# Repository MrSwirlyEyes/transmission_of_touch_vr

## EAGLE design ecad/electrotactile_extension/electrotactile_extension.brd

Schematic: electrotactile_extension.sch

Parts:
C37, C49, C63, C64, C66, C68, C69, C70, C76, C78, C80: 0.1uF/50V; CAPC1005X55_SMD-0402
C61: 0.1uF/50V; CAPC1608X95
C62: 0.1uF/250V/0805; CAPC2012X95_SMD-0805
C65: 100uF/10V; CAPCP3216X160
C71, C72, C73, C75, C77, C79: 10uF/6.3V; CAPC1005X55_SMD-0402
C74: 4.7uF/10V/0402; CAPC1005X55_SMD-0402
ET_INDEX_PIXEL1-1, ET_INDEX_PIXEL1-2, ET_INDEX_PIXEL1-3, ET_INDEX_PIXEL1-4, ET_INDEX_PIXEL2-1, ET_INDEX_PIXEL2-2, ET_INDEX_PIXEL2-3, ET_INDEX_PIXEL2-4, ET_INDEX_PIXEL3-1, ET_INDEX_PIXEL3-2, ET_INDEX_PIXEL3-3, ET_INDEX_PIXEL3-4, ET_INDEX_PIXEL4-1, ET_INDEX_PIXEL4-2, ET_INDEX_PIXEL4-3, ET_INDEX_PIXEL4-4: SPST-NO 170mA 250V; SOP254P609X203-4
ET_MIDDLE_PIXEL1-1, ET_MIDDLE_PIXEL1-2, ET_MIDDLE_PIXEL1-3, ET_MIDDLE_PIXEL1-4, ET_MIDDLE_PIXEL2-1, ET_MIDDLE_PIXEL2-2, ET_MIDDLE_PIXEL2-3, ET_MIDDLE_PIXEL2-4, ET_MIDDLE_PIXEL3-1, ET_MIDDLE_PIXEL3-2, ET_MIDDLE_PIXEL3-3, ET_MIDDLE_PIXEL3-4, ET_MIDDLE_PIXEL4-1, ET_MIDDLE_PIXEL4-2, ET_MIDDLE_PIXEL4-3, ET_MIDDLE_PIXEL4-4: SPST-NO 170mA 250V; SOP254P609X203-4
ET_PINKY_PIXEL1-1, ET_PINKY_PIXEL1-2, ET_PINKY_PIXEL1-3, ET_PINKY_PIXEL1-4, ET_PINKY_PIXEL2-1, ET_PINKY_PIXEL2-2, ET_PINKY_PIXEL2-3, ET_PINKY_PIXEL2-4, ET_PINKY_PIXEL3-1, ET_PINKY_PIXEL3-2, ET_PINKY_PIXEL3-3, ET_PINKY_PIXEL3-4, ET_PINKY_PIXEL4-1, ET_PINKY_PIXEL4-2, ET_PINKY_PIXEL4-3, ET_PINKY_PIXEL4-4: SPST-NO 170mA 250V; SOP254P609X203-4
ET_RING_PIXEL1-1, ET_RING_PIXEL1-2, ET_RING_PIXEL1-3, ET_RING_PIXEL1-4, ET_RING_PIXEL2-1, ET_RING_PIXEL2-2, ET_RING_PIXEL2-3, ET_RING_PIXEL2-4, ET_RING_PIXEL3-1, ET_RING_PIXEL3-2, ET_RING_PIXEL3-3, ET_RING_PIXEL3-4, ET_RING_PIXEL4-1, ET_RING_PIXEL4-2, ET_RING_PIXEL4-3, ET_RING_PIXEL4-4: SPST-NO 170mA 250V; SOP254P609X203-4
IC1: DRV8662; QFN50P400X400X100-21T270
INDEX_CONNECTOR: 1x17 MOLEX SMD RA; 1X17_MOLEX_0532611771_RA_SMD
J6, J7, J8, J9: 1x02 PTH VERT FEMALE; HDRVR2W64P254_1X2_558X254X850B
L3: 4.7uH/2A/1008; INDC2520X100
L4: 10uH/380mA; INDC1608X60-0603
MIDDLE_CONNECTOR: 1x17 MOLEX SMD RA; 1X17_MOLEX_0532611771_RA_SMD
MUX_INDEX: PCA9685; SOP65P650X110-28
MUX_MIDDLE: PCA9685; SOP65P650X110-28
MUX_PINKY: PCA9685; SOP65P650X110-28
MUX_RING: PCA9685; SOP65P650X110-28
NFET1: 2N7002DW; SOT65P230X110-6
OPAMP4: TLV2361_GP_20MA_7MHZ; SOT95P280X145-5
PINKY_CONNECTOR: 1x17 MOLEX SMD RA; 1X17_MOLEX_0532611771_RA_SMD
POT1: 100K; POTENTIOMETER_SQ-L5-W4.5-H2.3
R1: 768K; RESC1005X35_SMD-0402
R2: 115K; RESC1005X35_SMD-0402
R4: 220K; RESC1005X35_SMD-0402
R5: 100K; RESC1005X35_SMD-0402
R49, R57, R58, R59, R60, R61, R62, R63, R64, R65, R66, R67, R68, R69, R70, R71, R88, R89, R90, R91, R92, R93, R94, R95, R96, R97, R98, R99, R100, R101, R102, R103, R104, R105, R106, R107, R108, R109, R110, R111, R112, R113, R114, R115, R116, R117, R118, R119, R120, R121, R122, R123, R124, R125, R126, R127, R128, R129, R130, R131, R132, R133, R134, R135: 1K; RESC1005X35_SMD-0402
R54, R55, R56, R136, R137: 10K; RESC1005X35_SMD-0402
REXT: 7.5K; RESC1005X35_SMD-0402
RING_CONNECTOR: 1x17 MOLEX SMD RA; 1X17_MOLEX_0532611771_RA_SMD
SW1, SW3, SW4: 300mA/4V; SW_SLIDE_SPDT_RA_SMD_4V_300MA_6.7L-2.6W
VREG2: NCP1729 50mA; SOT95P275X100-6
VREG3: TPS62202 300mA 1.8V; SOT95P280X145-5
VREG-MCU1: TPS76833QDR 1A/3.3V; SOIC127P600X265-8

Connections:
1.8V: C73.1, C75.1, L4.2, OPAMP4.5 (V+), VREG2.2 (VIN), VREG2.5 (!SHDN), VREG3.4 (NC/FB)
3.3V: C37.1, C61.1, C65.A, C66.1, C68.1, C69.1, C70.1, C74.1, C77.1, C78.1, IC1.2 (VDD), L3.2, MUX_INDEX.2 (A1), MUX_INDEX.28 (VCC), MUX_MIDDLE.1 (A0), MUX_MIDDLE.2 (A1), MUX_MIDDLE.28 (VCC), MUX_PINKY.1 (A0), MUX_PINKY.3 (A2), MUX_PINKY.28 (VCC), MUX_RING.3 (A2), MUX_RING.28 (VCC), SW1.2, SW3.2, SW4.2, VREG3.1 (VIN), VREG3.3 (EN), VREG-MCU1.5 (VOUT), VREG-MCU1.6 (VOUT)
-1.8V: C72.1, OPAMP4.2 (V-), VREG2.1 (VOUT)
C+: C71.1, VREG2.6 (C+)
C-: C71.2, VREG2.3 (C-)
EN: IC1.20 (EN), R54.2, SW1.3 (S2)
FB: IC1.3 (FB), R1.1, R2.2, R4.2, R5.2
GAIN0: IC1.18 (GAIN0), NFET1.5 (G2), R55.2, SW3.3 (S2)
GAIN1: IC1.19 (GAIN1), NFET1.2 (G1), R56.2, SW4.3 (S2)
GND: C37.2, C49.2, C61.2, C62.2, C63.1, C65.K, C66.2, C68.2, C69.2, C70.2, C72.2, C73.2, C74.2, C75.2, C76.2, C77.2, C78.2, C79.2, C80.2, IC1.4 (GND), IC1.5 (GND), IC1.6 (GND), IC1.9 (GND), IC1.EP (GND), IC1.P$1 (GND), IC1.P$2 (GND), IC1.P$3 (GND), IC1.P$4 (GND), J6.2, MUX_INDEX.1 (A0), MUX_INDEX.3 (A2), MUX_INDEX.4 (A3), MUX_INDEX.5 (A4), MUX_INDEX.14 (GND), MUX_INDEX.23 (!OE), MUX_INDEX.24 (A5), MUX_INDEX.25 (EXTCLK), MUX_MIDDLE.3 (A2), MUX_MIDDLE.4 (A3), MUX_MIDDLE.5 (A4), MUX_MIDDLE.14 (GND), MUX_MIDDLE.23 (!OE), MUX_MIDDLE.24 (A5), MUX_MIDDLE.25 (EXTCLK), MUX_PINKY.2 (A1), MUX_PINKY.4 (A3), MUX_PINKY.5 (A4), MUX_PINKY.14 (GND), MUX_PINKY.23 (!OE), MUX_PINKY.24 (A5), MUX_PINKY.25 (EXTCLK), MUX_RING.1 (A0), MUX_RING.2 (A1), MUX_RING.4 (A3), MUX_RING.5 (A4), MUX_RING.14 (GND), MUX_RING.23 (!OE), MUX_RING.24 (A5), MUX_RING.25 (EXTCLK), NFET1.1 (S1), NFET1.4 (S2), R2.1, R49.1, R54.1, R55.1, R56.1, R57.1, R58.1, R59.1, R60.1, R61.1, R62.1, R63.1, R64.1, R65.1, R66.1, R67.1, R68.1, R69.1, R70.1, R71.1, R88.1, R89.1, R90.1, R91.1, R92.1, R93.1, R94.1, R95.1, R96.1, R97.1, R98.1, R99.1, R100.1, R101.1, R102.1, R103.1, R104.1, R105.1, R106.1, R107.1, R108.1, R109.1, R110.1, R111.1, R112.1, R113.1, R114.1, R115.1, R116.1, R117.1, R118.1, R119.1, R120.1, R121.1, R122.1, R123.1, R124.1, R125.1, R126.1, R127.1, R128.1, R129.1, R130.1, R131.1, R132.1, R133.1, R134.1, R135.1, R137.1, REXT.1, VREG2.4 (GND), VREG3.2 (GND), VREG-MCU1.1 (GND), VREG-MCU1.2 (!EN)
IN+: C64.1, OPAMP4.4 (OUT), POT1.1 (CCW), POT1.2 (S), R136.2
INDEX_IN1-1: ET_INDEX_PIXEL1-1.1, MUX_INDEX.6 (PWM0)
INDEX_IN1-2: ET_INDEX_PIXEL1-2.1, MUX_INDEX.8 (PWM2)
INDEX_IN1-3: ET_INDEX_PIXEL1-3.1, MUX_INDEX.10 (PWM4)
INDEX_IN1-4: ET_INDEX_PIXEL1-4.1, MUX_INDEX.12 (PWM6)
INDEX_IN2-1: ET_INDEX_PIXEL2-1.1, MUX_INDEX.7 (PWM1)
INDEX_IN2-2: ET_INDEX_PIXEL2-2.1, MUX_INDEX.9 (PWM3)
INDEX_IN2-3: ET_INDEX_PIXEL2-3.1, MUX_INDEX.11 (PWM5)
INDEX_IN2-4: ET_INDEX_PIXEL2-4.1, MUX_INDEX.13 (PWM7)
INDEX_IN3-1: ET_INDEX_PIXEL3-1.1, MUX_INDEX.15 (PWM8)
INDEX_IN3-2: ET_INDEX_PIXEL3-2.1, MUX_INDEX.17 (PWM10)
INDEX_IN3-3: ET_INDEX_PIXEL3-3.1, MUX_INDEX.19 (PWM12)
INDEX_IN3-4: ET_INDEX_PIXEL3-4.1, MUX_INDEX.21 (PWM14)
INDEX_IN4-1: ET_INDEX_PIXEL4-1.1, MUX_INDEX.16 (PWM9)
INDEX_IN4-2: ET_INDEX_PIXEL4-2.1, MUX_INDEX.18 (PWM11)
INDEX_IN4-3: ET_INDEX_PIXEL4-3.1, MUX_INDEX.20 (PWM13)
INDEX_IN4-4: ET_INDEX_PIXEL4-4.1, MUX_INDEX.22 (PWM15)
INDEX_OUT1-1: ET_INDEX_PIXEL1-1.3, INDEX_CONNECTOR.1
INDEX_OUT1-2: ET_INDEX_PIXEL1-2.3, INDEX_CONNECTOR.3
INDEX_OUT1-3: ET_INDEX_PIXEL1-3.3, INDEX_CONNECTOR.5
INDEX_OUT1-4: ET_INDEX_PIXEL1-4.3, INDEX_CONNECTOR.7
INDEX_OUT2-1: ET_INDEX_PIXEL2-1.3, INDEX_CONNECTOR.2
INDEX_OUT2-2: ET_INDEX_PIXEL2-2.3, INDEX_CONNECTOR.4
INDEX_OUT2-3: ET_INDEX_PIXEL2-3.3, INDEX_CONNECTOR.6
INDEX_OUT2-4: ET_INDEX_PIXEL2-4.3, INDEX_CONNECTOR.8
INDEX_OUT3-1: ET_INDEX_PIXEL3-1.3, INDEX_CONNECTOR.9
INDEX_OUT3-2: ET_INDEX_PIXEL3-2.3, INDEX_CONNECTOR.11
INDEX_OUT3-3: ET_INDEX_PIXEL3-3.3, INDEX_CONNECTOR.13
INDEX_OUT3-4: ET_INDEX_PIXEL3-4.3, INDEX_CONNECTOR.15
INDEX_OUT4-1: ET_INDEX_PIXEL4-1.3, INDEX_CONNECTOR.10
INDEX_OUT4-2: ET_INDEX_PIXEL4-2.3, INDEX_CONNECTOR.12
INDEX_OUT4-3: ET_INDEX_PIXEL4-3.3, INDEX_CONNECTOR.14
INDEX_OUT4-4: ET_INDEX_PIXEL4-4.3, INDEX_CONNECTOR.16
MIDDLE_IN1-1: ET_MIDDLE_PIXEL1-1.1, MUX_MIDDLE.21 (PWM14)
MIDDLE_IN1-2: ET_MIDDLE_PIXEL1-2.1, MUX_MIDDLE.19 (PWM12)
MIDDLE_IN1-3: ET_MIDDLE_PIXEL1-3.1, MUX_MIDDLE.17 (PWM10)
MIDDLE_IN1-4: ET_MIDDLE_PIXEL1-4.1, MUX_MIDDLE.15 (PWM8)
MIDDLE_IN2-1: ET_MIDDLE_PIXEL2-1.1, MUX_MIDDLE.22 (PWM15)
MIDDLE_IN2-2: ET_MIDDLE_PIXEL2-2.1, MUX_MIDDLE.20 (PWM13)
MIDDLE_IN2-3: ET_MIDDLE_PIXEL2-3.1, MUX_MIDDLE.18 (PWM11)
MIDDLE_IN2-4: ET_MIDDLE_PIXEL2-4.1, MUX_MIDDLE.16 (PWM9)
MIDDLE_IN3-1: ET_MIDDLE_PIXEL3-1.1, MUX_MIDDLE.12 (PWM6)
MIDDLE_IN3-2: ET_MIDDLE_PIXEL3-2.1, MUX_MIDDLE.10 (PWM4)
MIDDLE_IN3-3: ET_MIDDLE_PIXEL3-3.1, MUX_MIDDLE.8 (PWM2)
MIDDLE_IN3-4: ET_MIDDLE_PIXEL3-4.1, MUX_MIDDLE.6 (PWM0)
MIDDLE_IN4-1: ET_MIDDLE_PIXEL4-1.1, MUX_MIDDLE.13 (PWM7)
MIDDLE_IN4-2: ET_MIDDLE_PIXEL4-2.1, MUX_MIDDLE.11 (PWM5)
MIDDLE_IN4-3: ET_MIDDLE_PIXEL4-3.1, MUX_MIDDLE.9 (PWM3)
MIDDLE_IN4-4: ET_MIDDLE_PIXEL4-4.1, MUX_MIDDLE.7 (PWM1)
MIDDLE_OUT1-1: ET_MIDDLE_PIXEL1-1.3, MIDDLE_CONNECTOR.16
MIDDLE_OUT1-2: ET_MIDDLE_PIXEL1-2.3, MIDDLE_CONNECTOR.14
MIDDLE_OUT1-3: ET_MIDDLE_PIXEL1-3.3, MIDDLE_CONNECTOR.12
MIDDLE_OUT1-4: ET_MIDDLE_PIXEL1-4.3, MIDDLE_CONNECTOR.10
MIDDLE_OUT2-1: ET_MIDDLE_PIXEL2-1.3, MIDDLE_CONNECTOR.17
MIDDLE_OUT2-2: ET_MIDDLE_PIXEL2-2.3, MIDDLE_CONNECTOR.15
MIDDLE_OUT2-3: ET_MIDDLE_PIXEL2-3.3, MIDDLE_CONNECTOR.13
MIDDLE_OUT2-4: ET_MIDDLE_PIXEL2-4.3, MIDDLE_CONNECTOR.11
MIDDLE_OUT3-1: ET_MIDDLE_PIXEL3-1.3, MIDDLE_CONNECTOR.8
MIDDLE_OUT3-2: ET_MIDDLE_PIXEL3-2.3, MIDDLE_CONNECTOR.6
MIDDLE_OUT3-3: ET_MIDDLE_PIXEL3-3.3, MIDDLE_CONNECTOR.4
MIDDLE_OUT3-4: ET_MIDDLE_PIXEL3-4.3, MIDDLE_CONNECTOR.2
MIDDLE_OUT4-1: ET_MIDDLE_PIXEL4-1.3, MIDDLE_CONNECTOR.9
MIDDLE_OUT4-2: ET_MIDDLE_PIXEL4-2.3, MIDDLE_CONNECTOR.7
MIDDLE_OUT4-3: ET_MIDDLE_PIXEL4-3.3, MIDDLE_CONNECTOR.5
MIDDLE_OUT4-4: ET_MIDDLE_PIXEL4-4.3, MIDDLE_CONNECTOR.3
unnamed: ET_INDEX_PIXEL1-3.2, R58.2
unnamed: ET_INDEX_PIXEL1-1.2, R49.2
unnamed: IC1.7 (SW), IC1.8 (SW), L3.1
unnamed: C49.1, IC1.1 (VPUMP)
unnamed: C62.1, IC1.10 (VBST), IC1.11 (VBST), IC1.12 (PVDD), R1.2
unnamed: IC1.15 (REXT), REXT.2
unnamed: NFET1.6 (D1), R4.1
unnamed: NFET1.3 (D2), R5.1
unnamed: C64.2, IC1.17 (IN+)
unnamed: C63.2, IC1.16 (IN-)
unnamed: ET_INDEX_PIXEL1-2.2, R57.2
unnamed: ET_INDEX_PIXEL1-4.2, R59.2
unnamed: ET_INDEX_PIXEL2-1.2, R60.2
unnamed: ET_INDEX_PIXEL2-2.2, R61.2
unnamed: ET_INDEX_PIXEL2-3.2, R62.2
unnamed: ET_INDEX_PIXEL2-4.2, R63.2
unnamed: ET_INDEX_PIXEL3-1.2, R64.2
unnamed: ET_INDEX_PIXEL3-2.2, R65.2
unnamed: ET_INDEX_PIXEL3-3.2, R66.2
unnamed: ET_INDEX_PIXEL3-4.2, R67.2
unnamed: ET_INDEX_PIXEL4-1.2, R68.2
unnamed: ET_INDEX_PIXEL4-2.2, R69.2
unnamed: ET_INDEX_PIXEL4-3.2, R70.2
unnamed: ET_INDEX_PIXEL4-4.2, R71.2
unnamed: ET_MIDDLE_PIXEL1-1.2, R88.2
unnamed: ET_MIDDLE_PIXEL1-2.2, R89.2
unnamed: ET_MIDDLE_PIXEL1-3.2, R90.2
unnamed: ET_MIDDLE_PIXEL1-4.2, R91.2
unnamed: ET_MIDDLE_PIXEL2-1.2, R92.2
unnamed: ET_MIDDLE_PIXEL2-2.2, R93.2
unnamed: ET_MIDDLE_PIXEL2-3.2, R94.2
unnamed: ET_MIDDLE_PIXEL2-4.2, R95.2
unnamed: ET_MIDDLE_PIXEL3-1.2, R96.2
unnamed: ET_MIDDLE_PIXEL3-2.2, R97.2
unnamed: ET_MIDDLE_PIXEL3-3.2, R98.2
unnamed: ET_MIDDLE_PIXEL3-4.2, R99.2
unnamed: ET_MIDDLE_PIXEL4-1.2, R100.2
unnamed: ET_MIDDLE_PIXEL4-2.2, R101.2
unnamed: ET_MIDDLE_PIXEL4-3.2, R102.2
unnamed: ET_MIDDLE_PIXEL4-4.2, R103.2
unnamed: ET_RING_PIXEL1-1.2, R104.2
unnamed: ET_RING_PIXEL1-2.2, R105.2
unnamed: ET_RING_PIXEL1-3.2, R106.2
unnamed: ET_RING_PIXEL1-4.2, R107.2
unnamed: ET_RING_PIXEL2-1.2, R108.2
unnamed: ET_RING_PIXEL2-2.2, R109.2
unnamed: ET_RING_PIXEL2-3.2, R110.2
unnamed: ET_RING_PIXEL2-4.2, R111.2
unnamed: ET_RING_PIXEL3-1.2, R112.2
unnamed: ET_RING_PIXEL3-2.2, R113.2
unnamed: ET_RING_PIXEL3-3.2, R114.2
unnamed: ET_RING_PIXEL3-4.2, R115.2
unnamed: ET_RING_PIXEL4-1.2, R116.2
unnamed: ET_RING_PIXEL4-2.2, R117.2
unnamed: ET_RING_PIXEL4-3.2, R118.2
unnamed: ET_RING_PIXEL4-4.2, R119.2
unnamed: ET_PINKY_PIXEL1-1.2, R120.2
unnamed: ET_PINKY_PIXEL1-2.2, R121.2
unnamed: ET_PINKY_PIXEL1-3.2, R122.2
unnamed: ET_PINKY_PIXEL1-4.2, R123.2
unnamed: ET_PINKY_PIXEL2-1.2, R124.2
unnamed: ET_PINKY_PIXEL2-2.2, R125.2
unnamed: ET_PINKY_PIXEL2-3.2, R126.2
unnamed: ET_PINKY_PIXEL2-4.2, R127.2
unnamed: ET_PINKY_PIXEL3-1.2, R128.2
unnamed: ET_PINKY_PIXEL3-2.2, R129.2
unnamed: ET_PINKY_PIXEL3-3.2, R130.2
unnamed: ET_PINKY_PIXEL3-4.2, R131.2
unnamed: ET_PINKY_PIXEL4-1.2, R132.2
unnamed: ET_PINKY_PIXEL4-2.2, R133.2
unnamed: ET_PINKY_PIXEL4-3.2, R134.2
unnamed: ET_PINKY_PIXEL4-4.2, R135.2
unnamed: L4.1, VREG3.5 (VOUT)
unnamed: OPAMP4.1 (IN+), R136.1, R137.2
unnamed: C76.1, OPAMP4.3 (IN-), POT1.3 (CW)
PINKY_IN1-1: ET_PINKY_PIXEL1-1.1, MUX_PINKY.22 (PWM15)
PINKY_IN1-2: ET_PINKY_PIXEL1-2.1, MUX_PINKY.20 (PWM13)
PINKY_IN1-3: ET_PINKY_PIXEL1-3.1, MUX_PINKY.18 (PWM11)
PINKY_IN1-4: ET_PINKY_PIXEL1-4.1, MUX_PINKY.16 (PWM9)
PINKY_IN2-1: ET_PINKY_PIXEL2-1.1, MUX_PINKY.21 (PWM14)
PINKY_IN2-2: ET_PINKY_PIXEL2-2.1, MUX_PINKY.19 (PWM12)
PINKY_IN2-3: ET_PINKY_PIXEL2-3.1, MUX_PINKY.17 (PWM10)
PINKY_IN2-4: ET_PINKY_PIXEL2-4.1, MUX_PINKY.15 (PWM8)
PINKY_IN3-1: ET_PINKY_PIXEL3-1.1, MUX_PINKY.13 (PWM7)
PINKY_IN3-2: ET_PINKY_PIXEL3-2.1, MUX_PINKY.11 (PWM5)
PINKY_IN3-3: ET_PINKY_PIXEL3-3.1, MUX_PINKY.9 (PWM3)
PINKY_IN3-4: ET_PINKY_PIXEL3-4.1, MUX_PINKY.7 (PWM1)
PINKY_IN4-1: ET_PINKY_PIXEL4-1.1, MUX_PINKY.12 (PWM6)
PINKY_IN4-2: ET_PINKY_PIXEL4-2.1, MUX_PINKY.10 (PWM4)
PINKY_IN4-3: ET_PINKY_PIXEL4-3.1, MUX_PINKY.8 (PWM2)
PINKY_IN4-4: ET_PINKY_PIXEL4-4.1, MUX_PINKY.6 (PWM0)
PINKY_OUT1-1: ET_PINKY_PIXEL1-1.3, PINKY_CONNECTOR.16
PINKY_OUT1-2: ET_PINKY_PIXEL1-2.3, PINKY_CONNECTOR.14
PINKY_OUT1-3: ET_PINKY_PIXEL1-3.3, PINKY_CONNECTOR.12
PINKY_OUT1-4: ET_PINKY_PIXEL1-4.3, PINKY_CONNECTOR.10
PINKY_OUT2-1: ET_PINKY_PIXEL2-1.3, PINKY_CONNECTOR.17
PINKY_OUT2-2: ET_PINKY_PIXEL2-2.3, PINKY_CONNECTOR.15
PINKY_OUT2-3: ET_PINKY_PIXEL2-3.3, PINKY_CONNECTOR.13
PINKY_OUT2-4: ET_PINKY_PIXEL2-4.3, PINKY_CONNECTOR.11
PINKY_OUT3-1: ET_PINKY_PIXEL3-1.3, PINKY_CONNECTOR.8
PINKY_OUT3-2: ET_PINKY_PIXEL3-2.3, PINKY_CONNECTOR.6
PINKY_OUT3-3: ET_PINKY_PIXEL3-3.3, PINKY_CONNECTOR.4
PINKY_OUT3-4: ET_PINKY_PIXEL3-4.3, PINKY_CONNECTOR.2
PINKY_OUT4-1: ET_PINKY_PIXEL4-1.3, PINKY_CONNECTOR.9
PINKY_OUT4-2: ET_PINKY_PIXEL4-2.3, PINKY_CONNECTOR.7
PINKY_OUT4-3: ET_PINKY_PIXEL4-3.3, PINKY_CONNECTOR.5
PINKY_OUT4-4: ET_PINKY_PIXEL4-4.3, PINKY_CONNECTOR.3
RING_IN1-1: ET_RING_PIXEL1-1.1, MUX_RING.7 (PWM1)
RING_IN1-2: ET_RING_PIXEL1-2.1, MUX_RING.9 (PWM3)
RING_IN1-3: ET_RING_PIXEL1-3.1, MUX_RING.11 (PWM5)
RING_IN1-4: ET_RING_PIXEL1-4.1, MUX_RING.13 (PWM7)
RING_IN2-1: ET_RING_PIXEL2-1.1, MUX_RING.6 (PWM0)
RING_IN2-2: ET_RING_PIXEL2-2.1, MUX_RING.8 (PWM2)
RING_IN2-3: ET_RING_PIXEL2-3.1, MUX_RING.10 (PWM4)
RING_IN2-4: ET_RING_PIXEL2-4.1, MUX_RING.12 (PWM6)
RING_IN3-1: ET_RING_PIXEL3-1.1, MUX_RING.16 (PWM9)
RING_IN3-2: ET_RING_PIXEL3-2.1, MUX_RING.18 (PWM11)
RING_IN3-3: ET_RING_PIXEL3-3.1, MUX_RING.20 (PWM13)
RING_IN3-4: ET_RING_PIXEL3-4.1, MUX_RING.22 (PWM15)
RING_IN4-1: ET_RING_PIXEL4-1.1, MUX_RING.15 (PWM8)
RING_IN4-2: ET_RING_PIXEL4-2.1, MUX_RING.17 (PWM10)
RING_IN4-3: ET_RING_PIXEL4-3.1, MUX_RING.19 (PWM12)
RING_IN4-4: ET_RING_PIXEL4-4.1, MUX_RING.21 (PWM14)
RING_OUT1-1: ET_RING_PIXEL1-1.3, RING_CONNECTOR.1
RING_OUT1-2: ET_RING_PIXEL1-2.3, RING_CONNECTOR.3
RING_OUT1-3: ET_RING_PIXEL1-3.3, RING_CONNECTOR.5
RING_OUT1-4: ET_RING_PIXEL1-4.3, RING_CONNECTOR.7
RING_OUT2-1: ET_RING_PIXEL2-1.3, RING_CONNECTOR.2
RING_OUT2-2: ET_RING_PIXEL2-2.3, RING_CONNECTOR.4
RING_OUT2-3: ET_RING_PIXEL2-3.3, RING_CONNECTOR.6
RING_OUT2-4: ET_RING_PIXEL2-4.3, RING_CONNECTOR.8
RING_OUT3-1: ET_RING_PIXEL3-1.3, RING_CONNECTOR.9
RING_OUT3-2: ET_RING_PIXEL3-2.3, RING_CONNECTOR.11
RING_OUT3-3: ET_RING_PIXEL3-3.3, RING_CONNECTOR.13
RING_OUT3-4: ET_RING_PIXEL3-4.3, RING_CONNECTOR.15
RING_OUT4-1: ET_RING_PIXEL4-1.3, RING_CONNECTOR.10
RING_OUT4-2: ET_RING_PIXEL4-2.3, RING_CONNECTOR.12
RING_OUT4-3: ET_RING_PIXEL4-3.3, RING_CONNECTOR.14
RING_OUT4-4: ET_RING_PIXEL4-4.3, RING_CONNECTOR.16
SCL: J7.2, MUX_INDEX.26 (SCL), MUX_MIDDLE.26 (SCL), MUX_PINKY.26 (SCL), MUX_RING.26 (SCL)
SDA: J7.1, MUX_INDEX.27 (SDA), MUX_MIDDLE.27 (SDA), MUX_PINKY.27 (SDA), MUX_RING.27 (SDA)
V+: ET_INDEX_PIXEL1-1.4, ET_INDEX_PIXEL1-2.4, ET_INDEX_PIXEL1-3.4, ET_INDEX_PIXEL1-4.4, ET_INDEX_PIXEL2-1.4, ET_INDEX_PIXEL2-2.4, ET_INDEX_PIXEL2-3.4, ET_INDEX_PIXEL2-4.4, ET_INDEX_PIXEL3-1.4, ET_INDEX_PIXEL3-2.4, ET_INDEX_PIXEL3-3.4, ET_INDEX_PIXEL3-4.4, ET_INDEX_PIXEL4-1.4, ET_INDEX_PIXEL4-2.4, ET_INDEX_PIXEL4-3.4, ET_INDEX_PIXEL4-4.4, ET_MIDDLE_PIXEL1-1.4, ET_MIDDLE_PIXEL1-2.4, ET_MIDDLE_PIXEL1-3.4, ET_MIDDLE_PIXEL1-4.4, ET_MIDDLE_PIXEL2-1.4, ET_MIDDLE_PIXEL2-2.4, ET_MIDDLE_PIXEL2-3.4, ET_MIDDLE_PIXEL2-4.4, ET_MIDDLE_PIXEL3-1.4, ET_MIDDLE_PIXEL3-2.4, ET_MIDDLE_PIXEL3-3.4, ET_MIDDLE_PIXEL3-4.4, ET_MIDDLE_PIXEL4-1.4, ET_MIDDLE_PIXEL4-2.4, ET_MIDDLE_PIXEL4-3.4, ET_MIDDLE_PIXEL4-4.4, ET_PINKY_PIXEL1-1.4, ET_PINKY_PIXEL1-2.4, ET_PINKY_PIXEL1-3.4, ET_PINKY_PIXEL1-4.4, ET_PINKY_PIXEL2-1.4, ET_PINKY_PIXEL2-2.4, ET_PINKY_PIXEL2-3.4, ET_PINKY_PIXEL2-4.4, ET_PINKY_PIXEL3-1.4, ET_PINKY_PIXEL3-2.4, ET_PINKY_PIXEL3-3.4, ET_PINKY_PIXEL3-4.4, ET_PINKY_PIXEL4-1.4, ET_PINKY_PIXEL4-2.4, ET_PINKY_PIXEL4-3.4, ET_PINKY_PIXEL4-4.4, ET_RING_PIXEL1-1.4, ET_RING_PIXEL1-2.4, ET_RING_PIXEL1-3.4, ET_RING_PIXEL1-4.4, ET_RING_PIXEL2-1.4, ET_RING_PIXEL2-2.4, ET_RING_PIXEL2-3.4, ET_RING_PIXEL2-4.4, ET_RING_PIXEL3-1.4, ET_RING_PIXEL3-2.4, ET_RING_PIXEL3-3.4, ET_RING_PIXEL3-4.4, ET_RING_PIXEL4-1.4, ET_RING_PIXEL4-2.4, ET_RING_PIXEL4-3.4, ET_RING_PIXEL4-4.4, IC1.13 (OUT+)
V-: IC1.14 (OUT-), INDEX_CONNECTOR.17, MIDDLE_CONNECTOR.1, PINKY_CONNECTOR.1, RING_CONNECTOR.17
VBAT: C79.1, C80.1, J6.1, VREG-MCU1.3 (VIN), VREG-MCU1.4 (VIN)

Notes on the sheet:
TRANSMISSION OF TOUCH VR
TOUCH GLOVE
Rev 3
Designed by: MrSwirlyEyes
ANALOG VOLTAGE AMPLIFIER
ET ARRAY - INDEX
ET ARRAY - MIDDLE
0x44
ET ARRAY - RING
0x45
ET ARRAY - PINKY
SQW GENERATOR
ELECTROTACTILE ARRAYS
STAGE1
STAGE2
STAGE3
+3.3V VREG
+1.8V VREG
-1.8V VREG
0x42
0x43

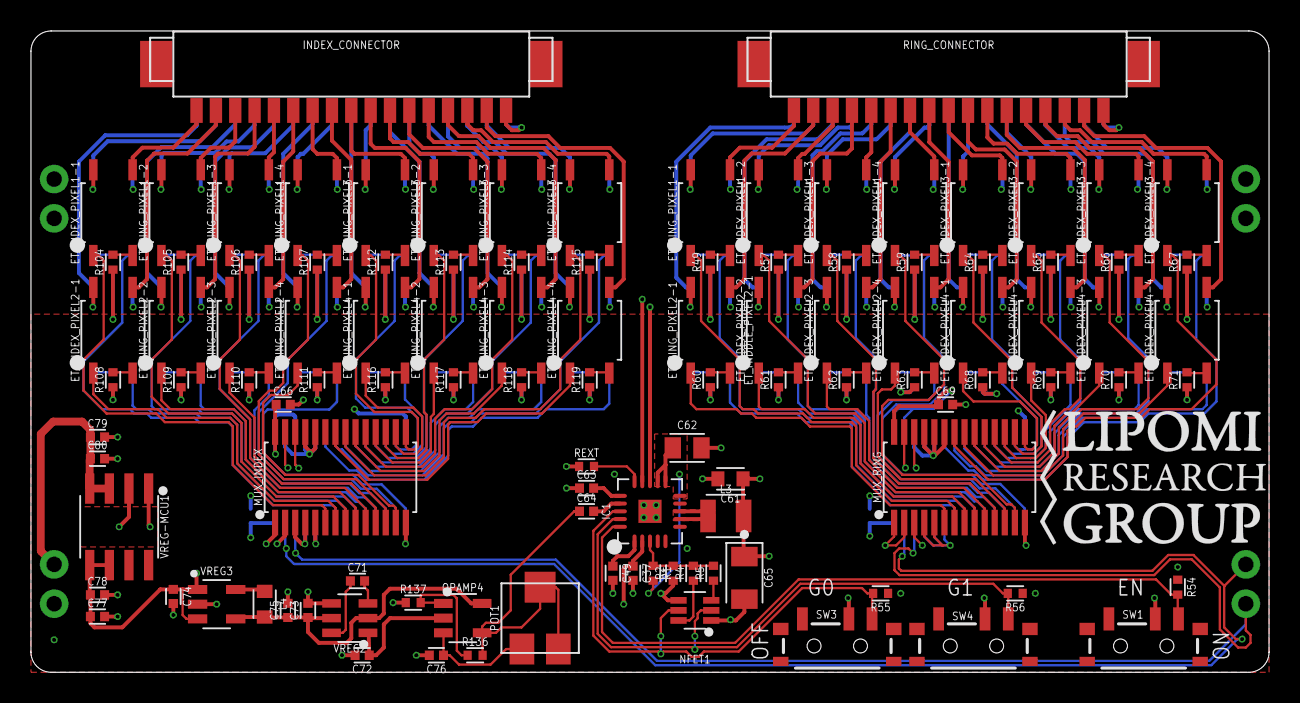
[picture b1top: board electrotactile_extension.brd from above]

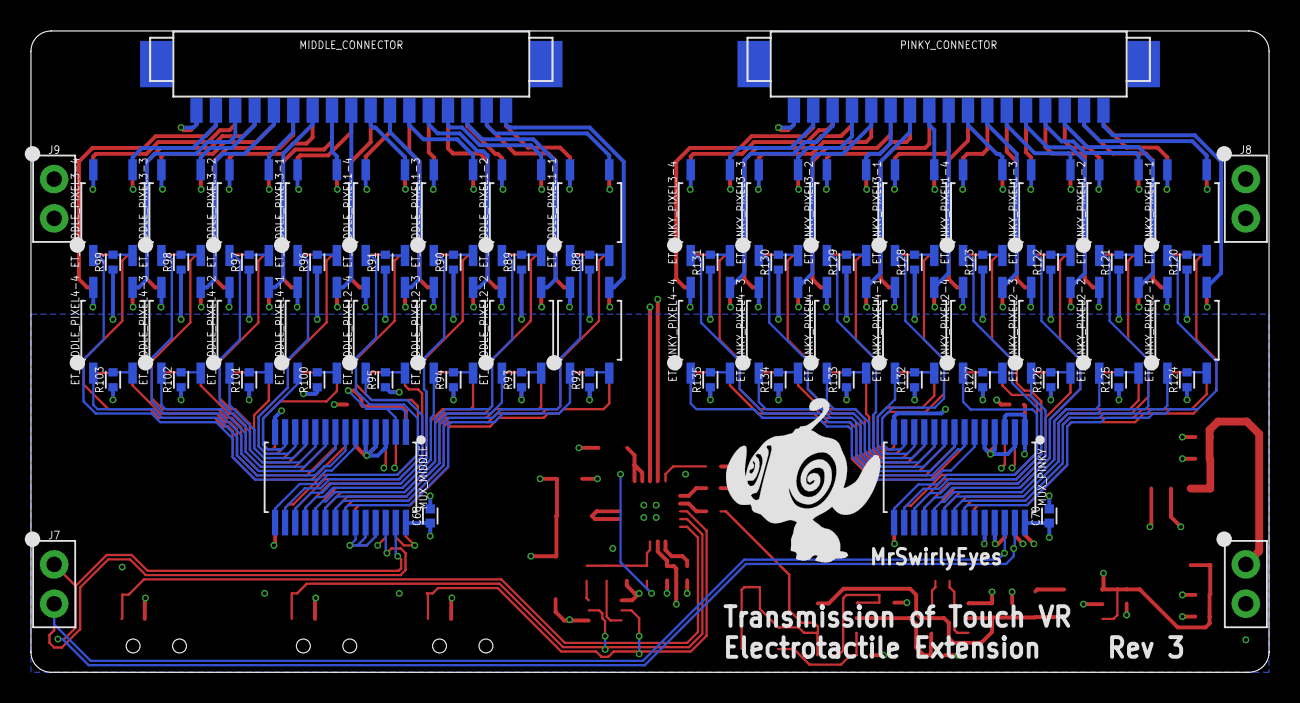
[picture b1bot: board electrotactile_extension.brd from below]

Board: 4 copper layers, 80.0 x 41.4 mm, 185 parts (75 on the bottom side), 219 nets.

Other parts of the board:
U$1: LRG-LOGO-2
U$2: MRSWIRLYEYES-LOGO

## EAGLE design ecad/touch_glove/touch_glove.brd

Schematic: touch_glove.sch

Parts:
ANT: 2.45GHz; ANTC6522X100
AVR_ISP: AVR ISP; HDRV6W64P254_2X3_762X508X838B
BALUN1: 50/100; RESCAXE65P200X125X95-6
BL_CONNECTOR: PTH VERT MALE; HDRV2W64P254_1X2_508X254X838B
BR_ANALOG: NET_BRIDGE
BR_CONNECTOR: PTH VERT MALE; HDRV2W64P254_1X2_508X254X838B
BR_NOISE: NET_BRIDGE
C1, C2, C3, C18, C21: 100uF/10V; CAPCP3216X160
C4, C6, C8, C11, C12, C15: 10uF/6.3V; CAPC1005X55_SMD-0402
C5, C7, C9, C10, C13, C14, C22, C23, C25, C27, C30, C38, C44, C45, C46, C47, C48, C50, C51, C52, C53, C54, C55, C56, C57, C58, C59, C60: 0.1uF/50V; CAPC1005X55_SMD-0402
C24, C26, C28, C29, C31, C32: 1uF/25V; CAPC1005X55_SMD-0402
C33, C34: 12pF/100V; CAPC1005X55_SMD-0402
C35: 0.75pF/50V; CAPC1005X55_SMD-0402
C36: 22pF/100V/0402; CAPC1005X55_SMD-0402
D2, D3: 1A/50V; SODFL3516X170
D4, D5, D6, D7, D8, D9, D10: 150mA/75V; DFN100X60X55-2
DEMUX1: CH16_MUX-DEMUX; SOP65P780X200-24
FLEX-INDEX: 10K; _MOLEX-0530470210_VERT_PITCH-1.25MM
FLEX-MIDDLE: 10K; _MOLEX-0530470210_VERT_PITCH-1.25MM
FLEX-PINKY: 10K; _MOLEX-0530470210_VERT_PITCH-1.25MM
FLEX-RING: 10K; _MOLEX-0530470210_VERT_PITCH-1.25MM
FLEX-THUMB: 10K; _MOLEX-0530470210_VERT_PITCH-1.25MM
FTDI: PTH RA VERT MALE; HDRRA6W64P254_1X6_1524X254X254B_FTDI
HBRIDGE-INDEX: DRV8837C 1A; WSON-8-PPAD
HBRIDGE-MIDDLE: DRV8837C 1A; WSON-8-PPAD
HBRIDGE-PINKY: DRV8837C 1A; WSON-8-PPAD
HBRIDGE-RING: DRV8837C 1A; WSON-8-PPAD
HBRIDGE-THUMB: DRV8837C 1A; WSON-8-PPAD
J9: PTH VERT MALE; HDRV2W64P254_1X2_508X254X838B
JP1: JUMPER_SMD_3-PAD_NO_SILK; SMT-JUMPER_3_NO_SILK
L1, L2: 10uH/380mA; INDC1608X60-0603
LED1: BLUE; LEDC1005X40_LED-0402
LED2: GREEN; LEDC1005X40_LED-0402
LED3: RED; LEDC1005X40_LED-0402
LIPO1: 7.4V; BATTERY_MOLEX-0530470210_VERT_PITCH-1.25MM
MCU: ATMEGA128RFA1; QFN50P900X900X90-64
OPAMP1, OPAMP2, OPAMP3: LM358; WSON-8-PPAD
PWM_DRIVER1: PCA9685; SOP65P650X110-28
Q1, Q2, Q3, Q4, Q5, Q6: MCH3474 4A/30V; SOTFL65P209X90-3
R1, R11, R12, R13, R14, R15, R32, R33, R34, R35, R36, R37, R38, R39, R40, R41, R42, R43, R44, R45, R46, R47, R48: 10K; RESC1005X35_SMD-0402
R2, R3: 4.7K; RESC1005X35_SMD-0402
R4, R5: 1K; RESC1005X35_SMD-0402
SW1: 4A/28V; SW_SLIDE_SPDT_RA_PTH_12.7L-9.5W
TEC-INDEX: PELTIER; _MOLEX-0530470210_VERT_PITCH-1.25MM
TEC-MIDDLE: PELTIER; _MOLEX-0530470210_VERT_PITCH-1.25MM
TEC-PINKY: PELTIER; _MOLEX-0530470210_VERT_PITCH-1.25MM
TEC-RING: PELTIER; _MOLEX-0530470210_VERT_PITCH-1.25MM
TEC-THUMB: PELTIER; _MOLEX-0530470210_VERT_PITCH-1.25MM
TL_CONNECTOR: PTH VERT MALE; HDRV2W64P254_1X2_508X254X838B
VIBE-INDEX: Molex VERT 1.25mm pitch; _MOLEX-0530470210_VERT_PITCH-1.25MM
VIBE-MIDDLE: Molex VERT 1.25mm pitch; _MOLEX-0530470210_VERT_PITCH-1.25MM
VIBE-PALM: Molex VERT 1.25mm pitch; _MOLEX-0530470210_VERT_PITCH-1.25MM
VIBE-PINKY: Molex VERT 1.25mm pitch; _MOLEX-0530470210_VERT_PITCH-1.25MM
VIBE-RING: Molex VERT 1.25mm pitch; _MOLEX-0530470210_VERT_PITCH-1.25MM
VIBE-THUMB: Molex VERT 1.25mm pitch; _MOLEX-0530470210_VERT_PITCH-1.25MM
VREG-ANALOG: MCP1700-1802 1.8V/200mA; SOT95P237X112-3_SOT-23-3
VREG-MCU: TPS76833QDR 1A/3.3V; SOIC127P600X265-8
VREG-TEC: 3A/1.8V; TO170P1363X457-6
VREG-VIBE: TL1963A-33 1.5A/3.3V; SOT229P700X180-4
XTAL: 16 MHz; OSCCC500X320X110_CRYSTAL

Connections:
1.8V: C21.A, C56.1, C57.1, C58.1, C59.1, C60.1, D3.A, HBRIDGE-INDEX.1 (VM), HBRIDGE-MIDDLE.1 (VM), HBRIDGE-PINKY.1 (VM), HBRIDGE-RING.1 (VM), HBRIDGE-THUMB.1 (VM), VREG-TEC.4 (VOUT), VREG-TEC.5 (SENSE)
3.3V: C18.A, D2.A, D5.K, D6.K, D7.K, D8.K, D9.K, D10.K, VIBE-INDEX.1 (+), VIBE-MIDDLE.1 (+), VIBE-PALM.1 (+), VIBE-PINKY.1 (+), VIBE-RING.1 (+), VIBE-THUMB.1 (+), VREG-VIBE.3 (VO)
+: LIPO1.+, SW1.P
A1.8V: C14.1, C15.1, JP1.1, MCU.62 (AREF), VREG-ANALOG.2 (VO)
A3.3V: C29.1, C30.1, JP1.3, L2.2, MCU.59 (EVDD)
AGND: BALUN1.5 (GND), C14.2, C15.2, C29.2, C30.2, C31.2, C35.2, C36.2, C38.2, C44.2, C45.2, C46.2, C47.2, C48.2, DEMUX1.7 (C2), DEMUX1.8 (C1), DEMUX1.9 (C0), DEMUX1.12 (GND), DEMUX1.15 (!EN), DEMUX1.16 (C15), DEMUX1.17 (C14), DEMUX1.18 (C13), DEMUX1.19 (C12), DEMUX1.20 (C11), DEMUX1.21 (C10), DEMUX1.22 (C9), DEMUX1.23 (C8), L1.2, MCU.7 (AVSS_RFP), MCU.10 (AVSS_RFN), MCU.58 (AVSS), MCU.61 (AVSS), MCU.EP (AVSS), MCU.P$1 (AVSS), MCU.P$2 (AVSS), MCU.P$3 (AVSS), MCU.P$4 (AVSS), MCU.P$5 (AVSS), OPAMP1.4 (V-), OPAMP1.GND (V-), OPAMP1.P$1 (V-), OPAMP1.P$2 (V-), OPAMP2.4 (V-), OPAMP2.GND (V-), OPAMP2.P$1 (V-), OPAMP2.P$2 (V-), OPAMP3.4 (V-), OPAMP3.GND (V-), OPAMP3.P$1 (V-), OPAMP3.P$2 (V-), R11.1, R12.1, R13.1, R14.1, R15.1
FLEX-INDEX: DEMUX1.3 (C6), OPAMP1.1 (OUT-A), OPAMP1.2 (IN-A-)
FLEX-MIDDLE: DEMUX1.4 (C5), OPAMP2.6 (IN-B-), OPAMP2.7 (OUT-B)
FLEX-PINKY: DEMUX1.6 (C3), OPAMP3.1 (OUT-A), OPAMP3.2 (IN-A-)
FLEX-RING: DEMUX1.5 (C4), OPAMP2.1 (OUT-A), OPAMP2.2 (IN-A-)
FLEX-THUMB: DEMUX1.2 (C7), OPAMP1.6 (IN-B-), OPAMP1.7 (OUT-B)
GND: AVR_ISP.GND, BL_CONNECTOR.2, BR_ANALOG.P$1, BR_NOISE.P$2, C10.2, C11.2, C12.2, C13.2, C23.2, C24.2, C25.2, C26.2, C27.2, C28.2, C32.2, C33.2, C34.2, C50.2, C51.2, C52.2, C53.2, C54.2, C55.2, FTDI.GND, LIPO1.-, MCU.11 (TST), MCU.20 (DVSS), MCU.24 (DVSS), MCU.33 (CLKI), MCU.35 (DVSS), MCU.45 (DVSS), MCU.55 (DVSS), PWM_DRIVER1.1 (A0), PWM_DRIVER1.2 (A1), PWM_DRIVER1.3 (A2), PWM_DRIVER1.4 (A3), PWM_DRIVER1.5 (A4), PWM_DRIVER1.14 (GND), PWM_DRIVER1.23 (!OE), PWM_DRIVER1.24 (A5), PWM_DRIVER1.25 (EXTCLK), R4.1, R5.1, R32.1, R33.1, R34.1, R35.1, R36.1, R37.1, R38.1, R39.1, R40.1, R41.1, R42.1, R43.1, R44.1, R45.1, R46.1, R47.1, VREG-ANALOG.1 (GND), VREG-MCU.1 (GND), VREG-MCU.2 (!EN)
LED_RX: LED3.A, MCU.42 ((PCINT6/OC1B/D34-PWM34)PB6)
LED_TX: LED2.A, MCU.43 ((PCINT7/OC0A/OC1C/D35-PWM35)PB7)
MISO: AVR_ISP.MISO, MCU.39 ((PDO/PCINT3/MISO/D12)PB3)
MOSI: AVR_ISP.MOSI, MCU.38 ((PDI/PCINT2/MOSI/D11)PB2)
unnamed: HBRIDGE-THUMB.3 (OUT2), TEC-THUMB.1 (HOT)
unnamed: D8.A, Q4.3 (D), VIBE-INDEX.2 (-)
unnamed: D9.A, Q5.3 (D), VIBE-THUMB.2 (-)
unnamed: D7.A, Q3.3 (D), VIBE-MIDDLE.2 (-)
unnamed: HBRIDGE-THUMB.2 (OUT1), TEC-THUMB.2 (COLD)
unnamed: HBRIDGE-INDEX.2 (OUT1), TEC-INDEX.2 (COLD)
unnamed: HBRIDGE-INDEX.3 (OUT2), TEC-INDEX.1 (HOT)
unnamed: HBRIDGE-MIDDLE.3 (OUT2), TEC-MIDDLE.1 (HOT)
unnamed: D6.A, Q2.3 (D), VIBE-RING.2 (-)
unnamed: HBRIDGE-MIDDLE.2 (OUT1), TEC-MIDDLE.2 (COLD)
unnamed: D5.A, Q1.3 (D), VIBE-PINKY.2 (-)
unnamed: HBRIDGE-RING.3 (OUT2), TEC-RING.1 (HOT)
unnamed: HBRIDGE-RING.2 (OUT1), TEC-RING.2 (COLD)
unnamed: HBRIDGE-PINKY.3 (OUT2), TEC-PINKY.1 (HOT)
unnamed: HBRIDGE-PINKY.2 (OUT1), TEC-PINKY.2 (COLD)
unnamed: D10.A, Q6.3 (D), VIBE-PALM.2 (-)
unnamed: C34.1, MCU.56 (XTAL2), XTAL.3 (XTAL2)
unnamed: C33.1, MCU.57 (XTAL1), XTAL.1 (XTAL1)
unnamed: FLEX-INDEX.2 (-), OPAMP1.3 (IN-A+), R12.2
unnamed: BR_ANALOG.P$2, L1.1
unnamed: FLEX-RING.2 (-), OPAMP2.3 (IN-A+), R14.2
unnamed: BALUN1.3 (OUT1), MCU.9 (RFN)
unnamed: BALUN1.4 (OUT2), MCU.8 (RFP)
unnamed: BALUN1.2 (GND), C36.1
unnamed: C22.1, FTDI.DTR
unnamed: LED1.K, R48.2
unnamed: LED2.K, R4.2
unnamed: LED3.K, R5.2
unnamed: C32.1, MCU.21 (DVDD), MCU.22 (DVDD)
unnamed: C31.1, MCU.60 (AVDD)
unnamed: FLEX-MIDDLE.2 (-), OPAMP2.5 (IN-B+), R13.2
unnamed: FLEX-THUMB.2 (-), OPAMP1.5 (IN-B+), R11.2
unnamed: FLEX-PINKY.2 (-), OPAMP3.3 (IN-A+), R15.2
NGND: BR_NOISE.P$1, C1.K, C2.K, C3.K, C4.2, C5.2, C6.2, C7.2, C8.2, C9.2, C18.K, C21.K, C56.2, C57.2, C58.2, C59.2, C60.2, HBRIDGE-INDEX.4 (GND), HBRIDGE-INDEX.GND, HBRIDGE-INDEX.P$1 (GND), HBRIDGE-INDEX.P$2 (GND), HBRIDGE-MIDDLE.4 (GND), HBRIDGE-MIDDLE.GND, HBRIDGE-MIDDLE.P$1 (GND), HBRIDGE-MIDDLE.P$2 (GND), HBRIDGE-PINKY.4 (GND), HBRIDGE-PINKY.GND, HBRIDGE-PINKY.P$1 (GND), HBRIDGE-PINKY.P$2 (GND), HBRIDGE-RING.4 (GND), HBRIDGE-RING.GND, HBRIDGE-RING.P$1 (GND), HBRIDGE-RING.P$2 (GND), HBRIDGE-THUMB.4 (GND), HBRIDGE-THUMB.GND, HBRIDGE-THUMB.P$1 (GND), HBRIDGE-THUMB.P$2 (GND), Q1.2 (S), Q2.2 (S), Q3.2 (S), Q4.2 (S), Q5.2 (S), Q6.2 (S), R48.1, TL_CONNECTOR.1, TL_CONNECTOR.2, VREG-TEC.3 (GND), VREG-TEC.TAB (GND), VREG-VIBE.2 (GND), VREG-VIBE.TAB (GND)
RESET: AVR_ISP.RESET, C22.2, D4.A, MCU.12 (RSTN), R1.1
RFSIG: ANT.1, BALUN1.1 (IN), C35.1
RX0: FTDI.TXO, MCU.46 ((PCINT8/RXD0/D0)PE0)
S0: DEMUX1.10 (S0), MCU.29 ((ICP1/D22)PD4)
S1: DEMUX1.11 (S1), MCU.30 ((XCK1/D23)PD5)
S2: DEMUX1.14 (S2), MCU.32 ((T0/D25)PD7)
S3: DEMUX1.13 (S3), MCU.31 ((T1/D24)PD6)
SCK: AVR_ISP.SCK, MCU.37 ((PCINT1/SCK/D13)PB1)
SCL: BR_CONNECTOR.2, MCU.25 ((INT0/SCL/D15)PD0), PWM_DRIVER1.26 (SCL), R2.1
SDA: BR_CONNECTOR.1, MCU.26 ((INT1/SDA/D14)PD1), PWM_DRIVER1.27 (SDA), R3.1
SIG: DEMUX1.1 (SIG), MCU.63 ((ADC0/A0*)PF0)
TEC-INDEX-COLD: HBRIDGE-INDEX.5 (IN2/EN), PWM_DRIVER1.17 (PWM10), R41.2
TEC-INDEX-HOT: HBRIDGE-INDEX.6 (IN1/PH), PWM_DRIVER1.18 (PWM11), R40.2
TEC-MIDDLE-COLD: HBRIDGE-MIDDLE.5 (IN2/EN), PWM_DRIVER1.19 (PWM12), R43.2
TEC-MIDDLE-HOT: HBRIDGE-MIDDLE.6 (IN1/PH), PWM_DRIVER1.20 (PWM13), R42.2
TEC-PINKY-COLD: HBRIDGE-PINKY.5 (IN2/EN), PWM_DRIVER1.13 (PWM7), R47.2
TEC-PINKY-HOT: HBRIDGE-PINKY.6 (IN1/PH), PWM_DRIVER1.12 (PWM6), R46.2
TEC-RING-COLD: HBRIDGE-RING.5 (IN2/EN), PWM_DRIVER1.21 (PWM14), R45.2
TEC-RING-HOT: HBRIDGE-RING.6 (IN1/PH), PWM_DRIVER1.22 (PWM15), R44.2
TEC-THUMB-COLD: HBRIDGE-THUMB.5 (IN2/EN), PWM_DRIVER1.15 (PWM8), R39.2
TEC-THUMB-HOT: HBRIDGE-THUMB.6 (IN1/PH), PWM_DRIVER1.16 (PWM9), R38.2
TX0: FTDI.RXI, MCU.47 ((TXD0/D1)PE1)
VBAT: BL_CONNECTOR.1, C1.A, C2.A, C3.A, C4.1, C5.1, C6.1, C7.1, C8.1, C9.1, D2.K, D3.K, LED1.A, SW1.S1, VREG-MCU.3 (VIN), VREG-MCU.4 (VIN), VREG-TEC.1 (!SHDN), VREG-TEC.2 (VIN), VREG-VIBE.1 (VI)
VCC: C10.1, C11.1, C12.1, C13.1, C23.1, C24.1, C25.1, C26.1, C27.1, C28.1, C50.1, C51.1, C52.1, C53.1, C54.1, C55.1, D4.K, HBRIDGE-INDEX.7 (NSLEEP), HBRIDGE-INDEX.8 (VCC), HBRIDGE-MIDDLE.7 (NSLEEP), HBRIDGE-MIDDLE.8 (VCC), HBRIDGE-PINKY.7 (NSLEEP), HBRIDGE-PINKY.8 (VCC), HBRIDGE-RING.7 (NSLEEP), HBRIDGE-RING.8 (VCC), HBRIDGE-THUMB.7 (NSLEEP), HBRIDGE-THUMB.8 (VCC), L2.1, MCU.23 (DEVDD), MCU.34 (DEVDD), MCU.44 (DEVDD), MCU.54 (DEVDD), PWM_DRIVER1.28 (VCC), R1.2, R2.2, R3.2, VREG-ANALOG.3 (VI), VREG-MCU.5 (VOUT), VREG-MCU.6 (VOUT)
VIBE-INDEX: PWM_DRIVER1.9 (PWM3), Q4.1 (G), R35.2
VIBE-MIDDLE: PWM_DRIVER1.8 (PWM2), Q3.1 (G), R34.2
VIBE-PALM: PWM_DRIVER1.11 (PWM5), Q6.1 (G), R37.2
VIBE-PINKY: PWM_DRIVER1.6 (PWM0), Q1.1 (G), R32.2
VIBE-RING: PWM_DRIVER1.7 (PWM1), Q2.1 (G), R33.2
VIBE-THUMB: PWM_DRIVER1.10 (PWM4), Q5.1 (G), R36.2
VSENSOR: C38.1, C44.1, C45.1, C46.1, C47.1, C48.1, DEMUX1.24 (VCC), FLEX-INDEX.1 (+), FLEX-MIDDLE.1 (+), FLEX-PINKY.1 (+), FLEX-RING.1 (+), FLEX-THUMB.1 (+), JP1.2, OPAMP1.8 (V+), OPAMP2.8 (V+), OPAMP3.8 (V+)

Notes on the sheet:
VIBROTACTILES
PELTIER DRIVERS
FLEX SENSORS
ANALOG DEMUX
PWM DRIVER
ATMEGA128RFA1
ACTUATORS
SENSORS
AVR ISP
FTDI
PROGRAMMER
POWER SYSTEM
MCU
LPF
TRANSMISSION OF TOUCH VR
TOUCH GLOVE
Rev 3
THERMOELECTRICS
Designed by: MrSwirlyEyes
LEDS

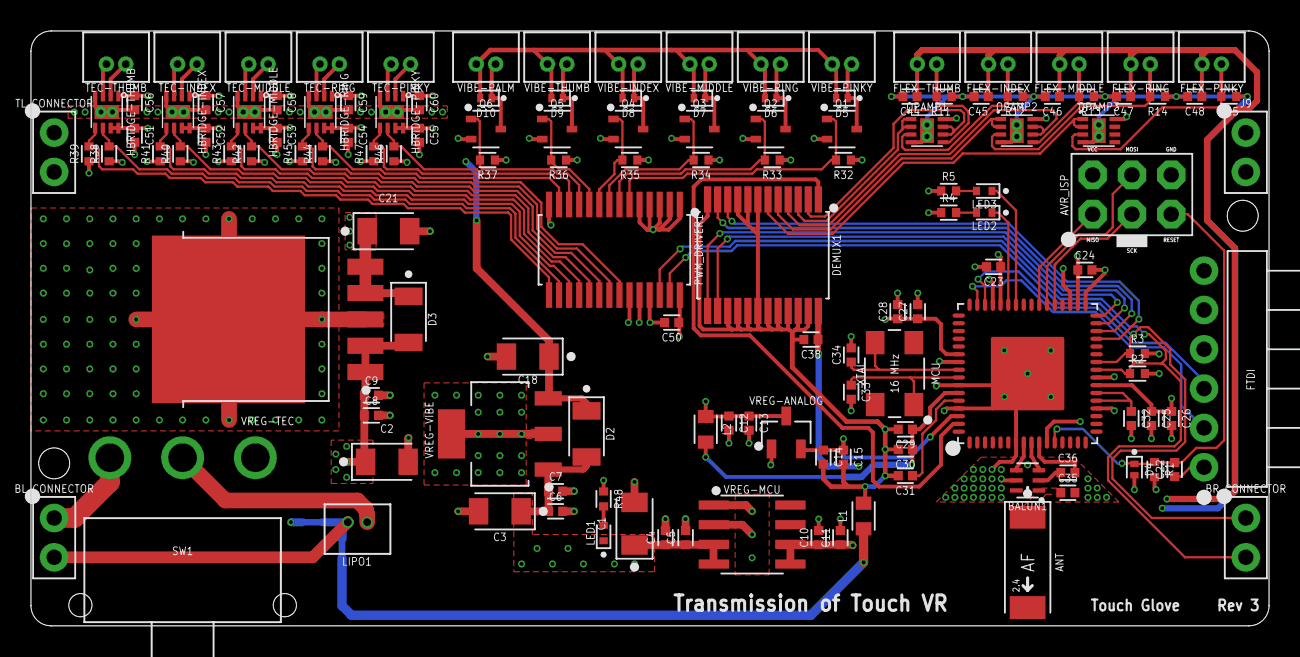
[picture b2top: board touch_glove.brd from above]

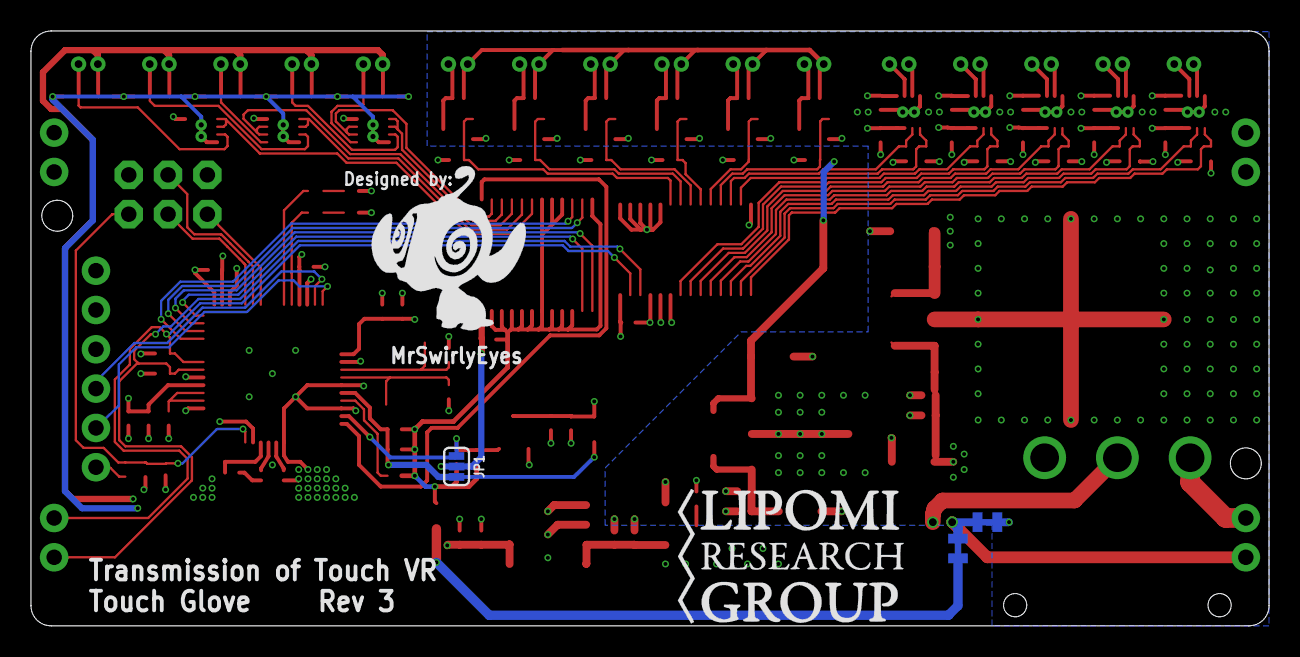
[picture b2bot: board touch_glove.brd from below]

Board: 4 copper layers, 80.0 x 38.4 mm, 143 parts (5 on the bottom side), 81 nets.

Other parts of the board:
U$1: LRG-LOGO-2
U$2: MRSWIRLYEYES-LOGO

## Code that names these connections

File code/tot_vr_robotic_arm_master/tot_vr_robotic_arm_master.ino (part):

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#define s1 3
#define s2 6
#define s3 5
#define sig_pin 2

CD74HC4067 multiplexer(s0, s1, s2, s3, sig_pin);



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///////////////////////////////////////
#define NUM_FSR 6

#define FSR_PINKY  0
#define FSR_RING   1
#define FSR_MIDDLE 2
#define FSR_INDEX  3
#define FSR_THUMB  4
#define FSR_PALM   5

#define FSR_MIN    0
#define FSR_MAX 4095
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#define FSR_MAX_PALM   800 //900

FSR fsr[NUM_FSR] = {
                      FSR(multiplexer,FSR_PINKY,FSR_MIN_PINKY,FSR_MAX_PINKY,FSR_MIN,FSR_MAX),
                      FSR(multiplexer,FSR_RING,FSR_MIN_RING,FSR_MAX_RING,FSR_MIN,FSR_MAX),
                      FSR(multiplexer,FSR_MIDDLE,FSR_MIN_MIDDLE,FSR_MAX_MIDDLE,FSR_MIN,FSR_MAX),
                      FSR(multiplexer,FSR_INDEX,FSR_MIN_INDEX,FSR_MAX_INDEX,FSR_MIN,FSR_MAX),
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#define NUM_TEMP 5
#define VCC 1.8

#define TEMP_PINKY  11
#define TEMP_RING   12
#define TEMP_MIDDLE 13
#define TEMP_INDEX  14
#define TEMP_THUMB  15

#define TEC_MAX_HOT 2048
#define TEC_MAX_COLD -4095
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// 32.0 C is approx max I could heat using fingers in ECE Makerspace

byte temp_pin[NUM_TEMP] = {
                            TEMP_PINKY,
                            TEMP_RING,
                            TEMP_MIDDLE,
                            TEMP_INDEX,
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                          };

TMP36 temp[NUM_TEMP] = {
                          TMP36(multiplexer,TEMP_PINKY,VCC,TEMP_MIN_LIMIT_COLD,TEMP_MAX_LIMIT_COLD,TEMP_MIN_LIMIT_HOT,TEMP_MAX_LIMIT_HOT,TEC_MAX_COLD,TEC_MAX_HOT),
                          TMP36(multiplexer,TEMP_RING,VCC,TEMP_MIN_LIMIT_COLD,TEMP_MAX_LIMIT_COLD,TEMP_MIN_LIMIT_HOT,TEMP_MAX_LIMIT_HOT,TEC_MAX_COLD,TEC_MAX_HOT),
                          TMP36(multiplexer,TEMP_MIDDLE,VCC,TEMP_MIN_LIMIT_COLD,TEMP_MAX_LIMIT_COLD,TEMP_MIN_LIMIT_HOT,TEMP_MAX_LIMIT_HOT,TEC_MAX_COLD,TEC_MAX_HOT),
                          TMP36(multiplexer,TEMP_INDEX,VCC,TEMP_MIN_LIMIT_COLD,TEMP_MAX_LIMIT_COLD,TEMP_MIN_LIMIT_HOT,TEMP_MAX_LIMIT_HOT,TEC_MAX_COLD,TEC_MAX_HOT),
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#define SERVO_MIN 0
#define SERVO_MAX 1023

#define SERVO_PINKY   8
#define SERVO_RING    9
#define SERVO_MIDDLE 10
#define SERVO_INDEX  11
#define SERVO_THUMB  12

#define SERVO_MIN_PINKY  180
#define SERVO_MIN_RING   180
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#define SERVO_CENTER ((SERVO_MAX_CENTER + SERVO_MIN_CENTER) / 2)

PCA9685Servo servo[NUM_SERVO] = {
                            PCA9685Servo(pwm_driver,SERVO_PINKY,SERVO_MIN,SERVO_MAX,SERVO_MIN_PINKY,SERVO_MAX_PINKY),
                            PCA9685Servo(pwm_driver,SERVO_RING,SERVO_MIN,SERVO_MAX,SERVO_MIN_RING,SERVO_MAX_RING),
                            PCA9685Servo(pwm_driver,SERVO_MIDDLE,SERVO_MIN,SERVO_MAX,SERVO_MIN_MIDDLE,SERVO_MAX_MIDDLE),
                            PCA9685Servo(pwm_driver,SERVO_INDEX,SERVO_MIN,SERVO_MAX,SERVO_MIN_INDEX,SERVO_MAX_INDEX),
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  }

  void print_tx_pkt() {
//    Serial.print("TX: (fsr_pinky,fsr_ring,fsr_middle,fsr_index,fsr_thumb,temp_pinky,temp_ring,temp_middle,temp_index,temp_thumb)=(");
    Serial.print("TX: (");
    for(int i = 0; i < NUM_FSR; i++) {
      Serial.print(pkt_tx.fsr[i]); Serial.print(",");  
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  }
  
  void print_rx_pkt() {
//    Serial.print("RX: (servo_pinky,servo_ring,servo_middle,servo_index,servo_thumb)=(");
    Serial.print("RX: (");
    for(int i = 0; i < NUM_SERVO; i++) {
      Serial.print(pkt_rx.servo[i]); Serial.print(",");      
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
